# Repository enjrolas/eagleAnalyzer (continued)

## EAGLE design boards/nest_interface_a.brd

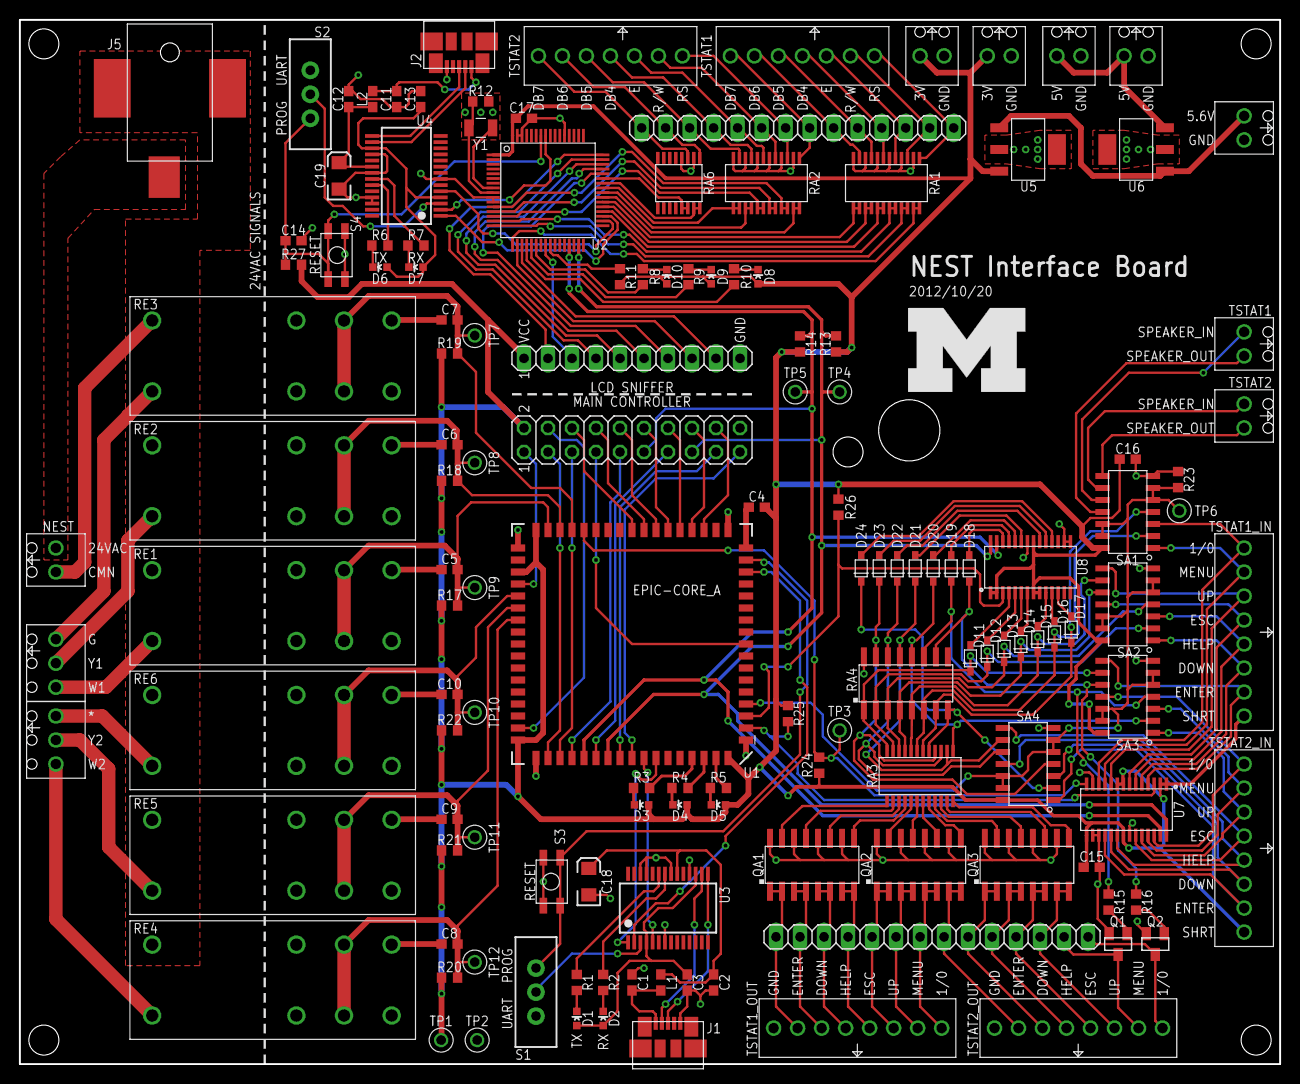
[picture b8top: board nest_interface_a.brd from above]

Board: 2 copper layers, 133.3 x 110.5 mm, 141 parts (0 on the bottom side), 194 nets.

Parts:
C1, C2, C3, C4, C5, C6, C7, C8, C9, C10, C11, C12, C13, C14, C15, C16: 0.1u; C0603
C17: 1u; C0603
C18, C19: 10u; EIA3216
D1, D3, D6, D8: RED; LED-0603
D2, D5, D7, D10: BLUE; LED-0603
D4, D9: GREEN; LED-0603
D11, D12, D13, D14, D15, D16, D17, D18, D19, D20, D21, D22, D23, D24: B5818WS-SCHOTTKY-DIODE; SOD-323
J1, J2: MOLEX_MICRO_USB_B_047346
J3: 2X10
J5: PJ-036A-SMT; PJ-0361-SMT
J6, J7, J8, J9, J10, J11, J12, J13: CONN_BLOCK_2
J14, J15: CONN_BLOCK_3
J16, J17: CONN_BLOCK_7
J18, J19, J20, J21: CONN_BLOCK_8
JP1: 1X10
JP2, JP3: 1X14
L1, L2: 0603
Q1, Q2: SOT23
QA1, QA2, QA3: MMPQ2222A; SOIC-16
R1, R2, R3, R4, R5, R6, R7, R8, R9, R10: 240; R0603
R11: 100k 0.1%; R0603
R12: 5.1M; R0603
R13, R14, R15, R16: 10k; R0603
R17, R18, R19, R20, R21, R22, R23, R24, R25, R26, R27: 100k; R0603
RA1, RA2, RA3: VSSR2403103; LSSOP-24
RA4: 766161104GP; SOIC-16
RA6: VSSR1603103; LSSOP-16
RE1, RE2, RE3, RE4, RE5, RE6: RT314524; S0418-CA
S1, S2: SWITCH-SPDT
S3, S4: EVQP2
SA1, SA2, SA3, SA4: TS12A44515DR; SOIC-14
TP1, TP2, TP3, TP4, TP5, TP6, TP7, TP8, TP9, TP10, TP11, TP12: TEST_POINT_0.040IN; TESTPOINT_0.040IN
U1: EPIC-CORE_A; EPIC-LCC68
U2: MSP430F1611IPM; PM/PAG64
U3, U4: FT232RL; SSOP28
U5: MPC1825; SOT-223-3
U6: TC1262; SOT-223-3
U7, U8: PCA9575; TSSOP28
U$1: UMICH_SOLID_LARGE; UMICH_SOLID_350MIL
Y1: FC-135_32.768KA-A3; FC-135

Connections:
5.6V_SUPPLY: J7.2, U5.1, U6.1
5V: J8.2, J9.2, U6.3
#KEYPAD_ENABLE: R23.1, SA1.5, SA1.6, SA1.12, SA1.13, SA2.5, SA2.6, SA2.12, SA2.13, SA3.5, SA3.6, SA3.12, SA3.13, SA4.5, SA4.6, SA4.12, SA4.13, TP6.TESTPOINT, U1.P$4
COMMON: J5.2, J5.3, J6.2, RE1.A2, RE2.A2, RE3.A2, RE4.A2, RE5.A2, RE6.A2
COOLING1_PIN: C6.1, R18.1, RE2.COMMON1, RE2.COMMON2, TP8.TESTPOINT, U1.P$32
COOLING2_PIN: C9.1, R21.1, RE5.COMMON1, RE5.COMMON2, TP11.TESTPOINT, U1.P$40
EPIC_ADC1: J3.18, U1.P$20
EPIC_ADC2: J3.16, U1.P$21
EPIC_ADC3: J3.14, U1.P$22
EPIC_ADC4: J3.12, U1.P$23
EPIC_ADC5: J3.10, U1.P$24
EPIC_ADC6/DAC0: J3.8, U1.P$25
EPIC_ADC7/DAC1: J3.6, U1.P$26
EPIC_MISO0: J3.13, U1.P$57
EPIC_P2.0: J3.1, U1.P$38
EPIC_P2.4: J3.5, U1.P$54
EPIC_P2.7: J3.3, U1.P$53
EPIC_P5.7: J3.7, U1.P$9
EPIC_STE0: J3.9, U1.P$55
EPIC_UART0RX: J3.19, U1.P$60
EPIC_UART0TX: J3.17, U1.P$59
FAN_PIN: C7.1, R19.1, RE3.COMMON1, RE3.COMMON2, TP7.TESTPOINT, U1.P$31
G: J14.1, RE3.A1
GND: C1.2, C2.2, C3.2, C5.2, C6.2, C7.2, C8.2, C9.2, C10.2, C11.2, C12.2, C13.2, C14.2, C15.2, C16.2, C17.2, C18.C, C19.C, J1.GND, J2.GND, J3.20, J7.1, J8.1, J9.1, J10.1, J11.1, J20.1, J21.1, JP1.10, Q1.2, Q2.2, QA1.10, QA1.12, QA1.14, QA1.16, QA2.10, QA2.12, QA2.14, QA2.16, QA3.10, QA3.12, QA3.14, QA3.16, R12.1, R23.2, RA1.2, RA1.4, RA1.6, RA1.8, RA1.10, RA1.12, RA2.2, RA2.4, RA2.6, RA2.8, RA2.10, RA2.12, RA4.16, RA6.2, RA6.4, RE1.NO1, RE1.NO2, RE2.NO1, RE2.NO2, RE3.NO1, RE3.NO2, RE4.NO1, RE4.NO2, RE5.NO1, RE5.NO2, RE6.NO1, RE6.NO2, S3.P$1, S3.P$3, S4.P$1, S4.P$3, SA1.7, SA2.7, SA3.7, SA4.7, TP2.TESTPOINT, U1.P$1, U1.P$18, U1.P$35, U1.P$52, U2.10, U2.11, U2.53, U2.62, U2.63, U3.7, U3.18, U3.21, U3.25, U3.26, U4.7, U4.18, U4.21, U4.25, U4.26, U5.2, U5.4, U6.2, U6.4, U7.13, U7.16, U7.17, U7.22, U8.15, U8.16, U8.22
HEATING1_PIN: C5.1, R17.1, RE1.COMMON1, RE1.COMMON2, TP9.TESTPOINT, U1.P$33
HEATING2_PIN: C8.1, R20.1, RE4.COMMON1, RE4.COMMON2, TP12.TESTPOINT, U1.P$41
I2C_SCL: J3.15, R13.2, TP4.TESTPOINT, U1.P$58, U2.31, U7.28, U8.28
I2C_SDA: J3.11, R14.2, TP5.TESTPOINT, U1.P$56, U2.29, U7.27, U8.27
LCDP_MISO1: JP1.5, U2.46
LCDP_MOSI1: JP1.6, U2.45
LCDP_P1.6: JP1.8, U2.18
LCDP_P1.7: JP1.9, U2.19
LCDP_P2.4: JP1.3, U2.24
LCDP_P5.4: JP1.2, U2.48
LCDP_STE1: JP1.7, U2.44
LCDP_UCLK1: JP1.4, U2.47
unnamed: C1.1, J1.VCC, L1.1
unnamed: D1.C, R1.2
unnamed: J1.D-, U3.16
unnamed: J1.D+, U3.15
unnamed: C2.1, C18.A, L1.2, U3.20
unnamed: D2.C, R2.2
unnamed: R10.1, U2.20
unnamed: U1.P$62, U3.1
unnamed: R1.1, U3.23
unnamed: R2.1, U3.22
unnamed: U1.P$61, U3.5
unnamed: D8.C, R10.2
unnamed: U1.P$15, U3.2
unnamed: C3.1, D1.A, D2.A, U3.4, U3.17
unnamed: QA2.11, RA3.19
unnamed: QA1.13, RA3.14
unnamed: C4.2, U1.P$17
unnamed: D3.C, R3.2
unnamed: D4.C, R4.2
unnamed: D5.C, R5.2
unnamed: R5.1, U1.P$67
unnamed: R4.1, U1.P$66
unnamed: R3.1, U1.P$65
unnamed: QA1.11, RA3.15
unnamed: QA1.9, RA3.16
unnamed: QA3.9, RA3.24
unnamed: QA3.15, RA3.21
unnamed: QA3.13, RA3.22
unnamed: QA3.11, RA3.23
unnamed: Q1.1, R15.1
unnamed: Q2.1, R16.1
unnamed: QA1.15, RA3.13
unnamed: QA2.15, RA3.17
unnamed: QA2.9, RA3.20
unnamed: U2.8, Y1.1
unnamed: C11.1, J2.VCC, L2.1
unnamed: J2.D-, U4.16
unnamed: J2.D+, U4.15
unnamed: C12.1, C19.A, L2.2, U4.20
unnamed: R6.1, U4.23
unnamed: R7.1, U4.22
unnamed: D6.C, R6.2
unnamed: D7.C, R7.2
unnamed: U2.35, U4.1
unnamed: U2.34, U4.5
unnamed: U2.57, U4.2
unnamed: C13.1, D6.A, D7.A, U4.4, U4.17
unnamed: R12.2, U2.9, Y1.2
unnamed: D9.C, R9.2
unnamed: R11.2, U2.25
unnamed: D10.C, R8.2
unnamed: R9.1, U2.21
unnamed: R8.1, U2.22
unnamed: QA2.13, RA3.18
RADIO_SFD: J3.4, U1.P$50
RH: J5.1, J6.1
RST: S1.1, S3.P$2, S3.P$4, U1.P$16
RST1: C14.1, R27.2, S2.1, S4.P$2, S4.P$4, U2.58
RST_USB: S1.2, U3.3
RST_USB1: S2.2, U4.3
STAR: J15.1, RE6.A1
STAR_PIN: C10.1, R22.1, RE6.COMMON1, RE6.COMMON2, TP10.TESTPOINT, U1.P$39
TSTAT1_DOWN_IN: J18.3, SA2.1, U7.5
TSTAT1_DOWN_OUT: J20.3, JP3.2, QA1.3, QA1.4
TSTAT1_DOWN_OUT_CTRL: D12.P$2, RA3.11, RA4.2, SA2.2
TSTAT1_DOWN_OUT_PIN: D12.P$1, U8.5
TSTAT1_ENTER_IN: J18.2, SA3.8, U7.4
TSTAT1_ENTER_OUT: J20.2, JP3.1, QA1.1, QA1.2
TSTAT1_ENTER_OUT_CTRL: D11.P$2, RA3.12, RA4.1, SA3.9
TSTAT1_ENTER_OUT_PIN: D11.P$1, U8.4
TSTAT1_ESC_IN: J18.5, SA2.11, U7.7
TSTAT1_ESC_OUT: J20.5, JP3.4, QA1.7, QA1.8
TSTAT1_ESC_OUT_CTRL: D14.P$2, RA3.9, RA4.4, SA2.10
TSTAT1_ESC_OUT_PIN: D14.P$1, U8.7
TSTAT1_HELP_IN: J18.4, SA2.3, U7.6
TSTAT1_HELP_OUT: J20.4, JP3.3, QA1.5, QA1.6
TSTAT1_HELP_OUT_CTRL: D13.P$2, RA3.10, RA4.3, SA2.4
TSTAT1_HELP_OUT_PIN: D13.P$1, U8.6
TSTAT1_LCD_DB4: J16.4, JP2.11, RA1.7
TSTAT1_LCD_DB4_PIN: RA1.17, RA1.18, U2.36
TSTAT1_LCD_DB5: J16.5, JP2.10, RA1.9
TSTAT1_LCD_DB5_PIN: RA1.15, RA1.16, U2.37
TSTAT1_LCD_DB6: J16.6, JP2.9, RA1.11
TSTAT1_LCD_DB6_PIN: RA1.13, RA1.14, U2.38
TSTAT1_LCD_DB7: J16.7, JP2.8, RA2.1
TSTAT1_LCD_DB7_PIN: RA2.23, RA2.24, U2.39
TSTAT1_LCD_E: J16.3, JP2.12, RA1.5
TSTAT1_LCD_E_PIN: RA1.19, RA1.20, U2.15
TSTAT1_LCD_R/W: J16.2, JP2.13, RA1.3
TSTAT1_LCD_R/W_PIN: RA1.21, RA1.22, U2.16
TSTAT1_LCD_RS: J16.1, JP2.14, RA1.1
TSTAT1_LCD_RS_PIN: RA1.23, RA1.24, U2.17
TSTAT1_MENU_IN: J18.7, SA1.1, U7.11
TSTAT1_MENU_OUT: J20.7, JP3.6, QA2.3, QA2.4
TSTAT1_MENU_OUT_CTRL: D16.P$2, RA3.7, RA4.6, SA1.2
TSTAT1_MENU_OUT_PIN: D16.P$1, U8.11
TSTAT1_ON/OFF_IN: J18.8, SA1.3, U7.12
TSTAT1_ON/OFF_OUT: J20.8, JP3.7, QA2.5, QA2.6
TSTAT1_ON/OFF_OUT_CTRL: D17.P$2, RA3.6, RA4.7, SA1.4
TSTAT1_ON/OFF_OUT_PIN: D17.P$1, U8.12
TSTAT1_SPEAKER_IN: J12.2, SA1.10
TSTAT1_SPEAKER_OUT: J12.1, SA1.11
TSTAT1_UP_IN: J18.6, SA2.8, U7.10
TSTAT1_UP_OUT: J20.6, JP3.5, QA2.1, QA2.2
TSTAT1_UP_OUT_CTRL: D15.P$2, RA3.8, RA4.5, SA2.9
TSTAT1_UP_OUT_PIN: D15.P$1, U8.10
TSTAT2_DOWN_IN: J19.3, SA4.3, U7.19
TSTAT2_DOWN_OUT: J21.3, JP3.9, QA3.1, QA3.2
TSTAT2_DOWN_OUT_CTRL: D23.P$2, RA3.4, RA4.15, SA4.4
TSTAT2_DOWN_OUT_PIN: D23.P$1, U8.19
TSTAT2_ENTER_IN: J19.2, SA4.1, U7.18
TSTAT2_ENTER_OUT: J21.2, JP3.8, QA2.7, QA2.8
TSTAT2_ENTER_OUT_CTRL: D24.P$2, RA3.5, RA4.8, SA4.2
TSTAT2_ENTER_OUT_PIN: D24.P$1, U8.18
TSTAT2_ESC_IN: J19.5, SA4.8, U7.23
TSTAT2_ESC_OUT: J21.5, JP3.11, QA3.5, QA3.6
TSTAT2_ESC_OUT_CTRL: D21.P$2, RA3.2, RA4.13, SA4.9
TSTAT2_ESC_OUT_PIN: D21.P$1, U8.23
TSTAT2_HELP_IN: J19.4, SA4.11, U7.20
TSTAT2_HELP_OUT: J21.4, JP3.10, QA3.3, QA3.4
TSTAT2_HELP_OUT_CTRL: D22.P$2, RA3.3, RA4.14, SA4.10
TSTAT2_HELP_OUT_PIN: D22.P$1, U8.20
TSTAT2_LCD_DB4: J17.4, JP2.4, RA2.9
TSTAT2_LCD_DB4_PIN: RA2.15, RA2.16, U2.40
TSTAT2_LCD_DB5: J17.5, JP2.3, RA2.11
TSTAT2_LCD_DB5_PIN: RA2.13, RA2.14, U2.41
TSTAT2_LCD_DB6: J17.6, JP2.2, RA6.1
TSTAT2_LCD_DB6_PIN: RA6.15, RA6.16, U2.42
TSTAT2_LCD_DB7: J17.7, JP2.1, RA6.3
TSTAT2_LCD_DB7_PIN: RA6.13, RA6.14, U2.43
TSTAT2_LCD_E: J17.3, JP2.5, RA2.7
TSTAT2_LCD_E_PIN: RA2.17, RA2.18, U2.14
TSTAT2_LCD_R/W: J17.2, JP2.6, RA2.5
TSTAT2_LCD_R/W_PIN: RA2.19, RA2.20, U2.13
TSTAT2_LCD_RS: J17.1, JP2.7, RA2.3
TSTAT2_LCD_RS_PIN: RA2.21, RA2.22, U2.12
TSTAT2_MENU_IN: J19.7, SA3.3, U7.25
TSTAT2_MENU_OUT: J21.7, JP3.13, Q1.3
TSTAT2_MENU_OUT_CTRL: D19.P$2, R15.2, RA4.11, SA3.4
TSTAT2_MENU_OUT_PIN: D19.P$1, U8.25
TSTAT2_ON/OFF_IN: J19.8, SA3.11, U7.26
TSTAT2_ON/OFF_OUT: J21.8, JP3.14, Q2.3
TSTAT2_ON/OFF_OUT_CTRL: D18.P$2, R16.2, RA4.10, SA3.10
TSTAT2_ON/OFF_OUT_PIN: D18.P$1, U8.26
TSTAT2_SPEAKER_IN: J13.2, SA1.9
TSTAT2_SPEAKER_OUT: J13.1, SA1.8
TSTAT2_UP_IN: J19.6, SA3.1, U7.24
TSTAT2_UP_OUT: J21.6, JP3.12, QA3.7, QA3.8
TSTAT2_UP_OUT_CTRL: D20.P$2, RA3.1, RA4.12, SA3.2
TSTAT2_UP_OUT_PIN: D20.P$1, U8.24
TSTAT_IN_I2C_INT: R24.2, TP3.TESTPOINT, U1.P$30, U7.14
TSTAT_IN_I2C_RST: R25.2, U1.P$2, U7.3
TSTAT_OUT_I2C_RST: R26.2, U1.P$3, U8.3
VCC: C4.1, C15.1, C16.1, C17.1, D3.A, D4.A, D5.A, D8.A, D9.A, D10.A, J3.2, J10.2, J11.2, J18.1, J19.1, JP1.1, R11.1, R13.1, R14.1, R17.2, R18.2, R19.2, R20.2, R21.2, R22.2, R24.1, R25.1, R26.1, R27.1, SA1.14, SA2.14, SA3.14, SA4.14, TP1.TESTPOINT, U1.P$34, U1.P$37, U1.P$51, U1.P$68, U2.1, U2.64, U5.3, U7.1, U7.2, U7.8, U7.9, U7.15, U7.21, U8.1, U8.2, U8.8, U8.9, U8.21
W1: J14.3, RE1.A1
W2: J15.3, RE4.A1
Y1: J14.2, RE2.A1
Y2: J15.2, RE5.A1
